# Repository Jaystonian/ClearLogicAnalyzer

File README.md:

74LXC8T245-based logic analyzer with better PCB design.

A vast improvement on https://github.com/gusmanb/logicanalyzer

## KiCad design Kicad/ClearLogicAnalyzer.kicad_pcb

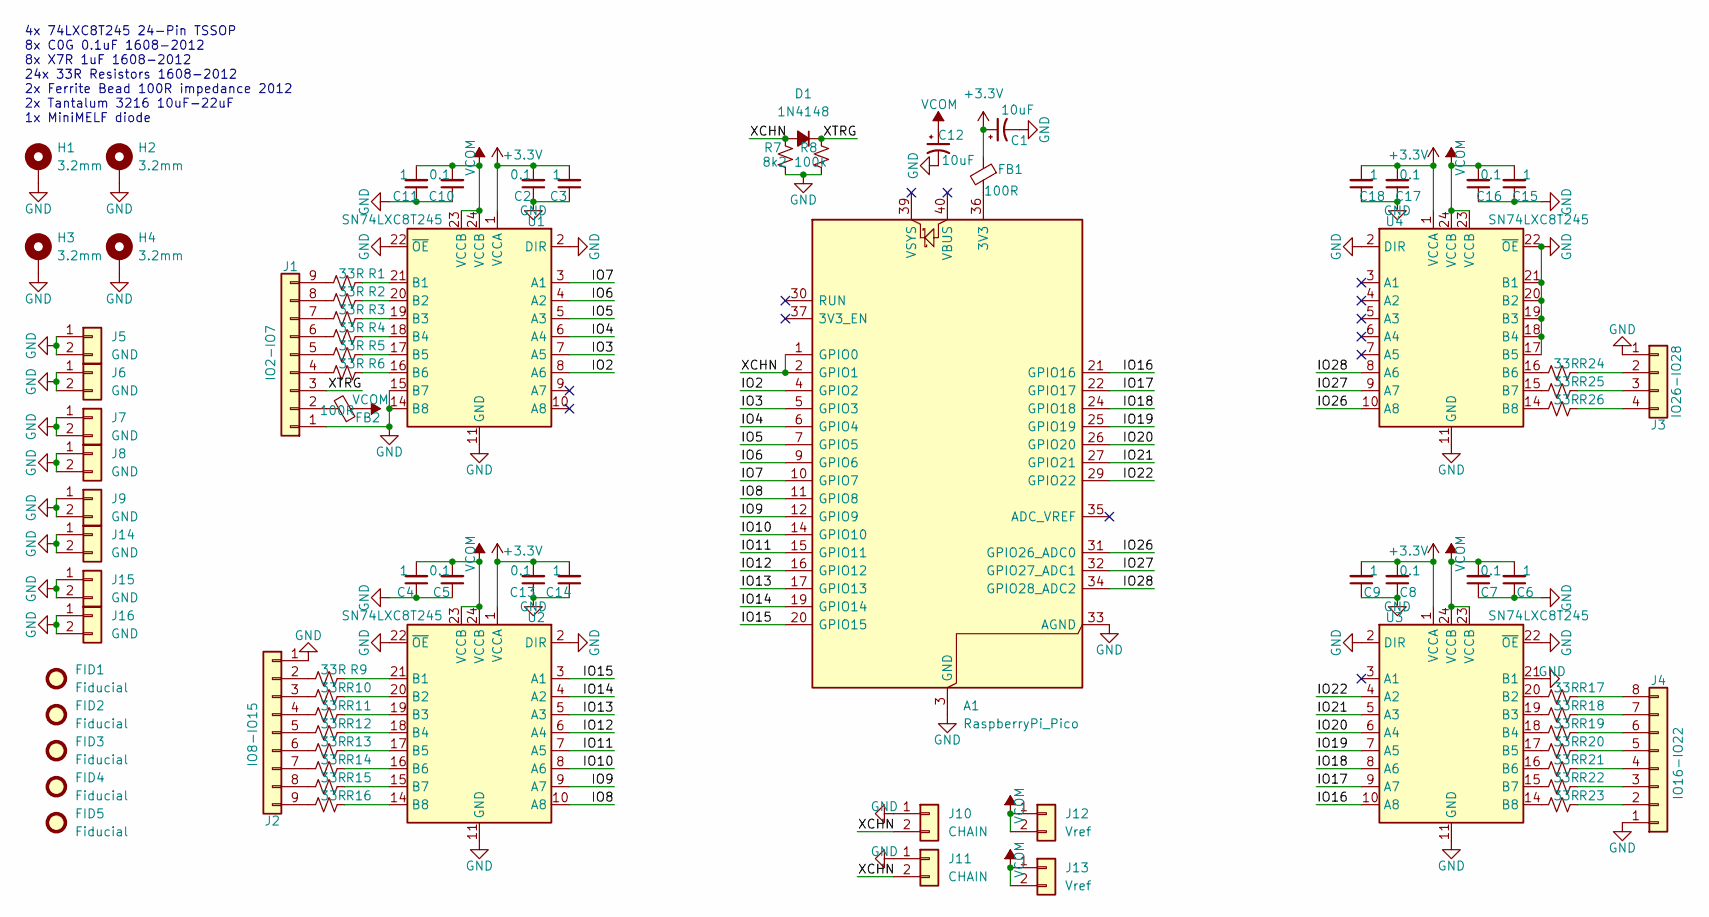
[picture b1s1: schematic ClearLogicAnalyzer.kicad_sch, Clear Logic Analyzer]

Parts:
A1: RaspberryPi_Pico; RaspberryPi_Pico_THT
C1, C12: 10uF; CP_EIA-3216-18_Kemet-A
C2, C5, C7, C8, C10, C13, C16, C17: 0.1; C_0805_2012Metric_Pad1.18x1.45mm_HandSolder
C3, C4, C6, C9, C11, C14, C15, C18: 1; C_0805_2012Metric_Pad1.18x1.45mm_HandSolder
D1: 1N4148; D_MiniMELF
FB1, FB2: 100R; R_0805_2012Metric_Pad1.20x1.40mm_HandSolder
FID1, FID2, FID3, FID4, FID5: Fiducial; Fiducial_0.5mm_Mask1mm
H1, H2, H3, H4: 3.2mm; MountingHole_3.2mm_M3_Pad_Via
J1: IO2-IO7; PinHeader_1x09_P2.54mm_Vertical
J2: IO8-IO15; PinHeader_1x09_P2.54mm_Vertical
J3: IO26-IO28; PinHeader_1x04_P2.54mm_Vertical
J4: IO16-IO22; PinHeader_1x08_P2.54mm_Vertical
J5, J6, J7, J8, J9, J14, J15, J16: GND; PinHeader_1x02_P2.54mm_Vertical
J10, J11: CHAIN; PinHeader_1x02_P2.54mm_Vertical
J12, J13: Vref; PinHeader_1x02_P2.54mm_Vertical
R1, R2, R3, R4, R5, R6, R9, R10, R11, R12, R13, R14, R15, R16, R17, R18, R19, R20, R21, R22, R23, R24, R25, R26: 33R; R_0805_2012Metric_Pad1.20x1.40mm_HandSolder
R7: 8k2; R_0805_2012Metric_Pad1.20x1.40mm_HandSolder
R8: 100k; R_0805_2012Metric_Pad1.20x1.40mm_HandSolder
U1, U2, U3, U4: SN74LXC8T245; TSSOP-24_4.4x7.8mm_P0.65mm

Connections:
+3.3V: C1.1, C2.2, C3.2, C8.2, C9.2, C13.2, C14.2, C17.2, C18.2, FB1.1, U1.1 (VCCA), U2.1 (VCCA), U3.1 (VCCA), U4.1 (VCCA)
/IO2: A1.4 (GPIO2), U1.8 (A6)
/IO3: A1.5 (GPIO3), U1.7 (A5)
/IO4: A1.6 (GPIO4), U1.6 (A4)
/IO5: A1.7 (GPIO5), U1.5 (A3)
/IO6: A1.9 (GPIO6), U1.4 (A2)
/IO7: A1.10 (GPIO7), U1.3 (A1)
/IO8: A1.11 (GPIO8), U2.10 (A8)
/IO9: A1.12 (GPIO9), U2.9 (A7)
/IO10: A1.14 (GPIO10), U2.8 (A6)
/IO11: A1.15 (GPIO11), U2.7 (A5)
/IO12: A1.16 (GPIO12), U2.6 (A4)
/IO13: A1.17 (GPIO13), U2.5 (A3)
/IO14: A1.19 (GPIO14), U2.4 (A2)
/IO15: A1.20 (GPIO15), U2.3 (A1)
/IO16: A1.21 (GPIO16), U3.10 (A8)
/IO17: A1.22 (GPIO17), U3.9 (A7)
/IO18: A1.24 (GPIO18), U3.8 (A6)
/IO19: A1.25 (GPIO19), U3.7 (A5)
/IO20: A1.26 (GPIO20), U3.6 (A4)
/IO21: A1.27 (GPIO21), U3.5 (A3)
/IO22: A1.29 (GPIO22), U3.4 (A2)
/IO26: A1.31 (GPIO26_ADC0), U4.10 (A8)
/IO27: A1.32 (GPIO27_ADC1), U4.9 (A7)
/IO28: A1.34 (GPIO28_ADC2), U4.8 (A6)
/XCHN: A1.1 (GPIO0), A1.2 (GPIO1), D1.2 (A), J10.2, J11.2, R7.2
/XTRG: D1.1 (K), J1.3, R8.2
GND: A1.3 (GND), A1.8 (GND), A1.13 (GND), A1.18 (GND), A1.23 (GND), A1.28 (GND), A1.33 (AGND), A1.38 (GND), C1.2, C2.1, C3.1, C4.1, C5.1, C6.1, C7.1, C8.1, C9.1, C10.1, C11.1, C12.2, C13.1, C14.1, C15.1, C16.1, C17.1, C18.1, H1.1, H2.1, H3.1, H4.1, J1.1, J2.1, J3.1, J4.1, J5.1, J5.2, J6.1, J6.2, J7.1, J7.2, J8.1, J8.2, J9.1, J9.2, J10.1, J11.1, J14.1, J14.2, J15.1, J15.2, J16.1, J16.2, R7.1, R8.1, U1.2 (DIR), U1.11 (GND), U1.12 (GND), U1.13 (GND), U1.14 (B8), U1.15 (B7), U1.22 (~OE), U2.2 (DIR), U2.11 (GND), U2.12 (GND), U2.13 (GND), U2.22 (~OE), U3.2 (DIR), U3.11 (GND), U3.12 (GND), U3.13 (GND), U3.21 (B1), U3.22 (~OE), U4.2 (DIR), U4.11 (GND), U4.12 (GND), U4.13 (GND), U4.17 (B5), U4.18 (B4), U4.19 (B3), U4.20 (B2), U4.21 (B1), U4.22 (~OE)
unnamed: A1.36 (3V3), FB1.2
unnamed: FB2.2, J1.2
unnamed: J1.4, R6.1
unnamed: J1.5, R5.1
unnamed: J1.6, R4.1
unnamed: J1.7, R3.1
unnamed: J1.8, R2.1
unnamed: J1.9, R1.1
unnamed: J2.2, R9.1
unnamed: J2.3, R10.1
unnamed: J2.4, R11.1
unnamed: J2.5, R12.1
unnamed: J2.6, R13.1
unnamed: J2.7, R14.1
unnamed: J2.8, R15.1
unnamed: J2.9, R16.1
unnamed: J3.2, R24.2
unnamed: J3.3, R25.2
unnamed: J3.4, R26.2
unnamed: J4.2, R23.2
unnamed: J4.3, R22.2
unnamed: J4.4, R21.2
unnamed: J4.5, R20.2
unnamed: J4.6, R19.2
unnamed: J4.7, R18.2
unnamed: J4.8, R17.2
unnamed: R1.2, U1.21 (B1)
unnamed: R2.2, U1.20 (B2)
unnamed: R3.2, U1.19 (B3)
unnamed: R4.2, U1.18 (B4)
unnamed: R5.2, U1.17 (B5)
unnamed: R6.2, U1.16 (B6)
unnamed: R9.2, U2.21 (B1)
unnamed: R10.2, U2.20 (B2)
unnamed: R11.2, U2.19 (B3)
unnamed: R12.2, U2.18 (B4)
unnamed: R13.2, U2.17 (B5)
unnamed: R14.2, U2.16 (B6)
unnamed: R15.2, U2.15 (B7)
unnamed: R16.2, U2.14 (B8)
unnamed: R17.1, U3.20 (B2)
unnamed: R18.1, U3.19 (B3)
unnamed: R19.1, U3.18 (B4)
unnamed: R20.1, U3.17 (B5)
unnamed: R21.1, U3.16 (B6)
unnamed: R22.1, U3.15 (B7)
unnamed: R23.1, U3.14 (B8)
unnamed: R24.1, U4.16 (B6)
unnamed: R25.1, U4.15 (B7)
unnamed: R26.1, U4.14 (B8)
VCOM: C4.2, C5.2, C6.2, C7.2, C10.2, C11.2, C12.1, C15.2, C16.2, FB2.1, J12.1, J12.2, J13.1, J13.2, U1.23 (VCCB), U1.24 (VCCB), U2.23 (VCCB), U2.24 (VCCB), U3.23 (VCCB), U3.24 (VCCB), U4.23 (VCCB), U4.24 (VCCB)

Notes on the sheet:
4x 74LXC8T245 24-Pin TSSOP 8x C0G 0.1uF 1608-2012 8x X7R 1uF 1608-2012 24x 33R Resistors 1608-2012 2x Ferrite Bead 100R impedance 2012 2x Tantalum 3216 10uF-22uF 1x MiniMELF diode

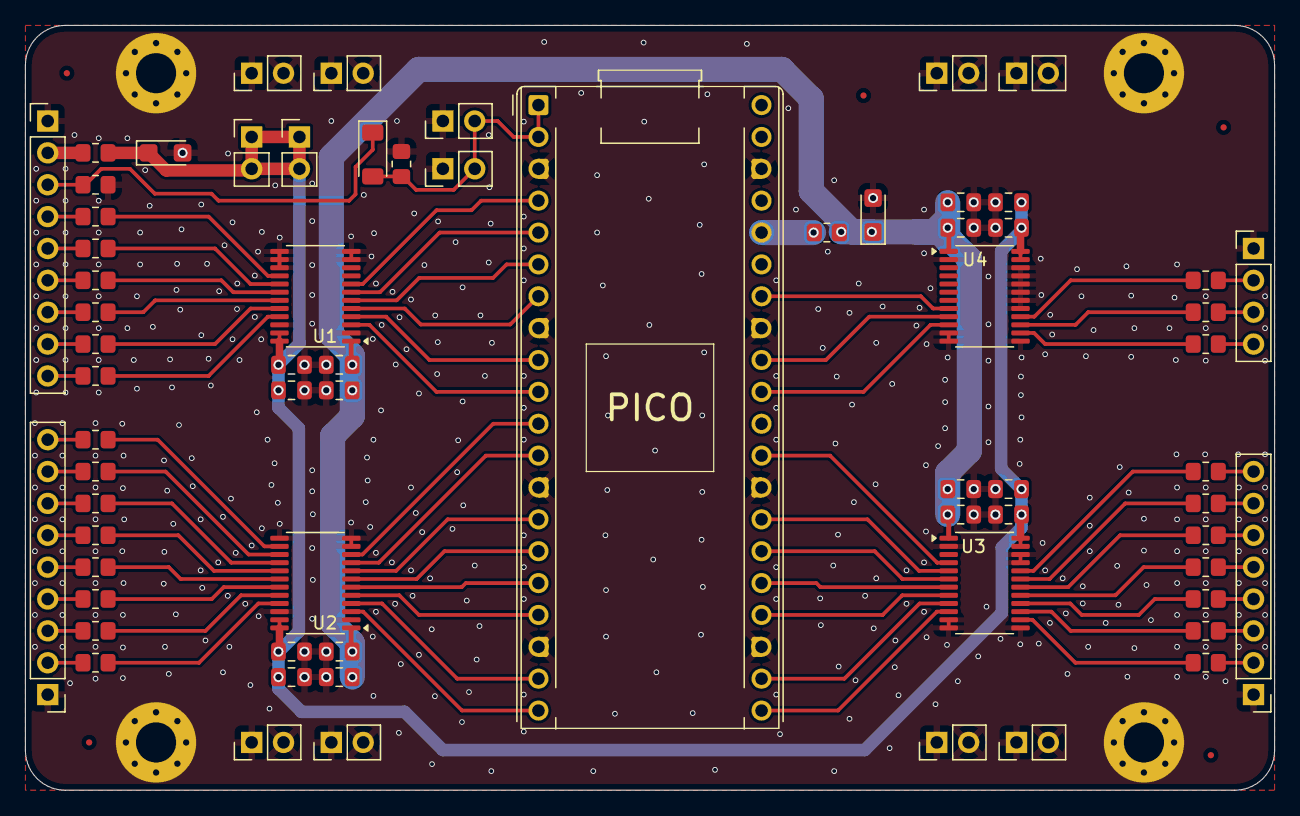
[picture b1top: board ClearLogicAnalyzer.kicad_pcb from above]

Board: 2 copper layers, 99.6 x 61.0 mm, 77 parts (0 on the bottom side), 79 nets.

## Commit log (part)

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2026-01-20 Revise README for ClearLogicAnalyzer project
    Expanded the README to include detailed design goals, key features, electrical overview, and project status.
2026-01-20 Update simultaneous channels
2026-01-20 Update input protection details in README
2026-01-20 Add MIT License to the project
